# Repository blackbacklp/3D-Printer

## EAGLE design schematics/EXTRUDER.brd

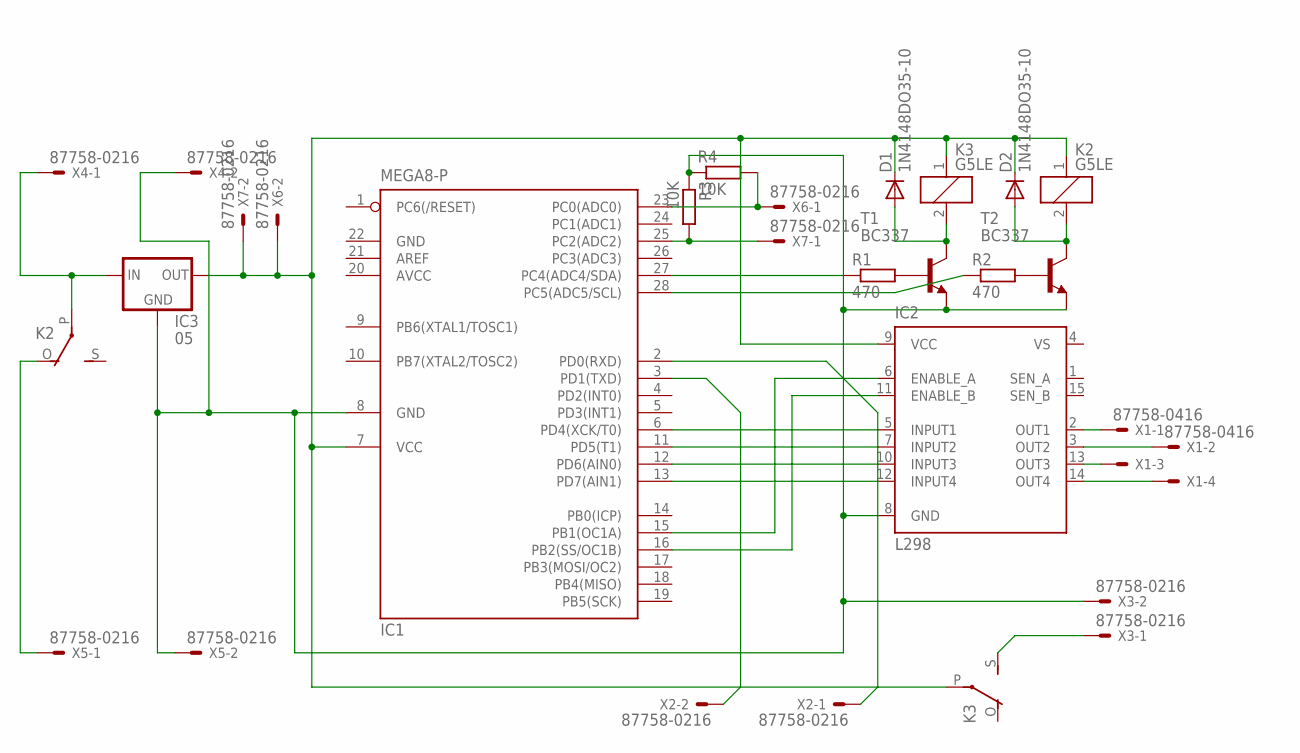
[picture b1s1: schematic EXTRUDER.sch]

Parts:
D1, D2: 1N4148DO35-10; DO35-10
IC1: MEGA8-P; DIL28-3
IC2: L298; MULTIWATT-15
IC3: 05; 78XXL
K2, K3: G5LE
R1, R2: 470; 0204/5
R3, R4: 10K; 0204/5
T1, T2: BC337; TO92
X1: 87758-0416
X2, X3, X4, X5, X6, X7: 87758-0216

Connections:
AVCC: IC1.20 (AVCC)
GND: IC1.22 (GND)
unnamed: IC1.6 (PD4(XCK/T0)), IC2.5 (INPUT1)
unnamed: IC1.11 (PD5(T1)), IC2.7 (INPUT2)
unnamed: IC1.12 (PD6(AIN0)), IC2.10 (INPUT3)
unnamed: IC1.13 (PD7(AIN1)), IC2.12 (INPUT4)
unnamed: IC1.15 (PB1(OC1A)), IC2.6 (ENABLE_A)
unnamed: IC1.16 (PB2(SS/OC1B)), IC2.11 (ENABLE_B)
unnamed: D1.A, K3.2, T1.3 (C)
unnamed: IC1.23 (PC0(ADC0)), R4.2, X6.1
unnamed: D2.A, K2.2, T2.3 (C)
unnamed: D1.C, D2.C, IC1.7 (VCC), IC2.9 (VCC), IC3.OUT, K2.1, K3.1, K3.P, X6.2, X7.2
unnamed: R1.2, T1.2 (B)
unnamed: R2.2, T2.2 (B)
unnamed: IC1.27 (PC4(ADC4/SDA)), R1.1
unnamed: IC1.28 (PC5(ADC5/SCL)), R2.1
unnamed: IC1.3 (PD1(TXD)), X2.2
unnamed: IC1.2 (PD0(RXD)), X2.1
unnamed: IC2.2 (OUT1), X1.1
unnamed: IC2.3 (OUT2), X1.2
unnamed: IC2.13 (OUT3), X1.3
unnamed: IC2.14 (OUT4), X1.4
unnamed: K3.S, X3.1
unnamed: IC3.IN, K2.P, X4.1
unnamed: IC1.25 (PC2(ADC2)), R3.2, X7.1
unnamed: K2.O, X5.1
unnamed: IC1.8 (GND), IC2.8 (GND), IC3.GND, R3.1, R4.1, T1.1 (E), T2.1 (E), X3.2, X4.2, X5.2
VS: IC2.4 (VS)

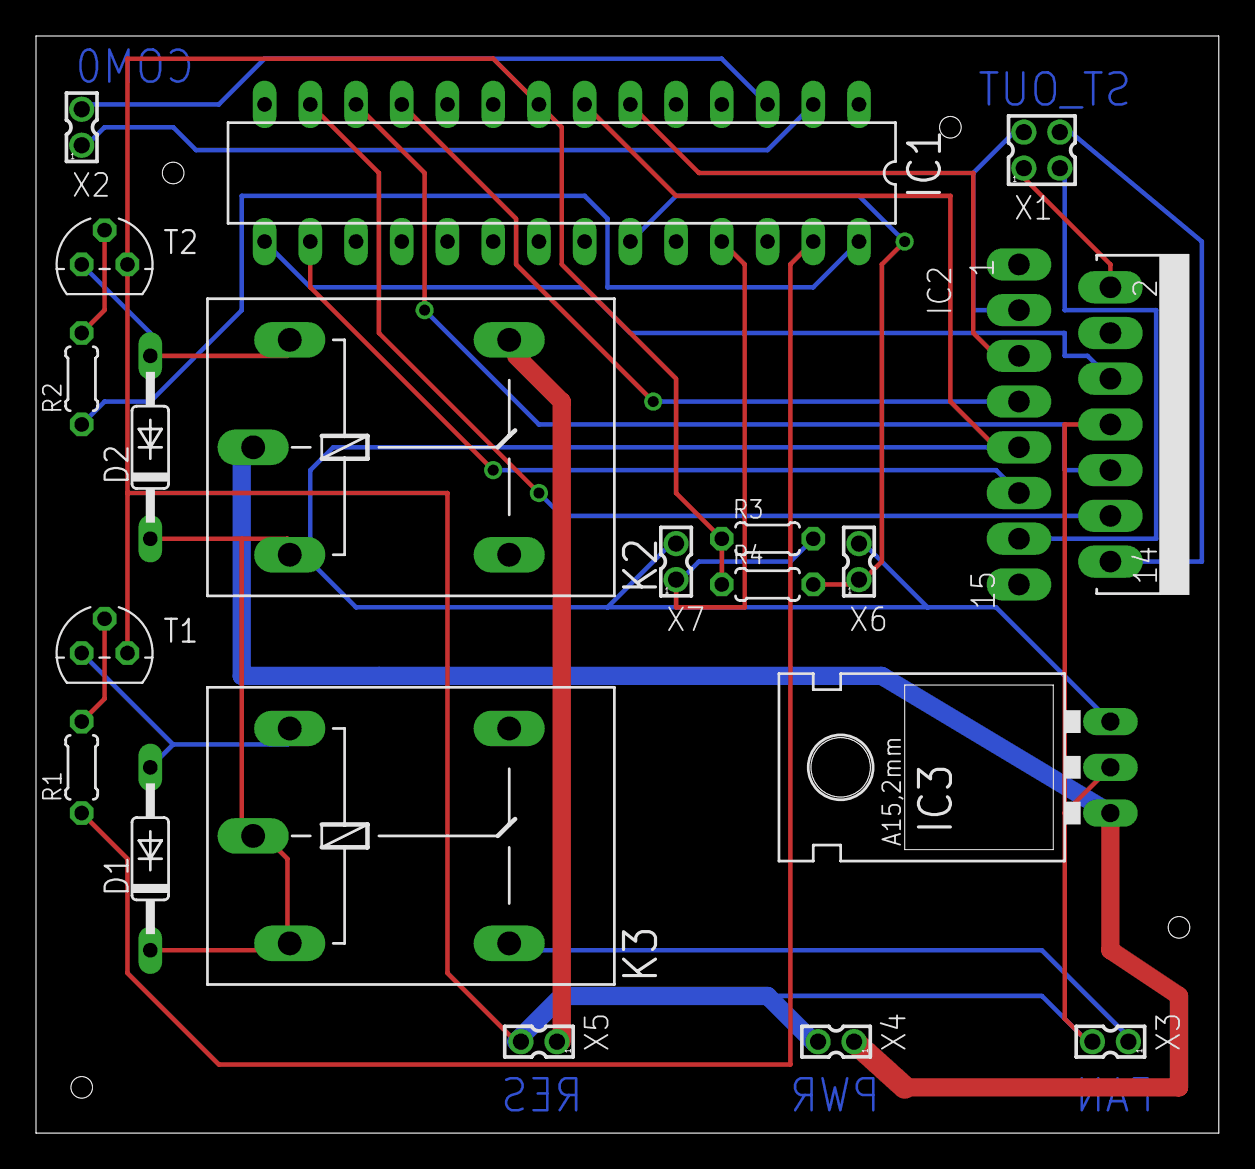
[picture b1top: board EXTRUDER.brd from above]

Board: 2 copper layers, 65.7 x 61.0 mm, 20 parts (0 on the bottom side), 25 nets.

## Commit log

2014-04-11 First Code Version
2014-04-11 First schematics of the extruder
